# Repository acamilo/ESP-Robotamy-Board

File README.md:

## ESP8266 Robotics Board ##

The ESP-Robotics-Board is an arduino compatible board intended for building robots out of old toys as well as many other simple robotics projects.

- ESP8266-12 wifi module
- Dual L9110 (800ma) H-Bridge ICs
 - For small DC motors.
- ALC5628 DAC+AMP
 - Drive an 8 0hm speaker
- Screw Terminals to attatch motors, bettery, speakers
 - Strip wires in up-cycled toys and attatch directly to the board.
- Drive up to 8 servoes
 - 1 motor, 6 servoes
 - 2 motors, 4 servoes
 - 8 GPIO for sensors
  -i2c broken out
  -ADC broken out

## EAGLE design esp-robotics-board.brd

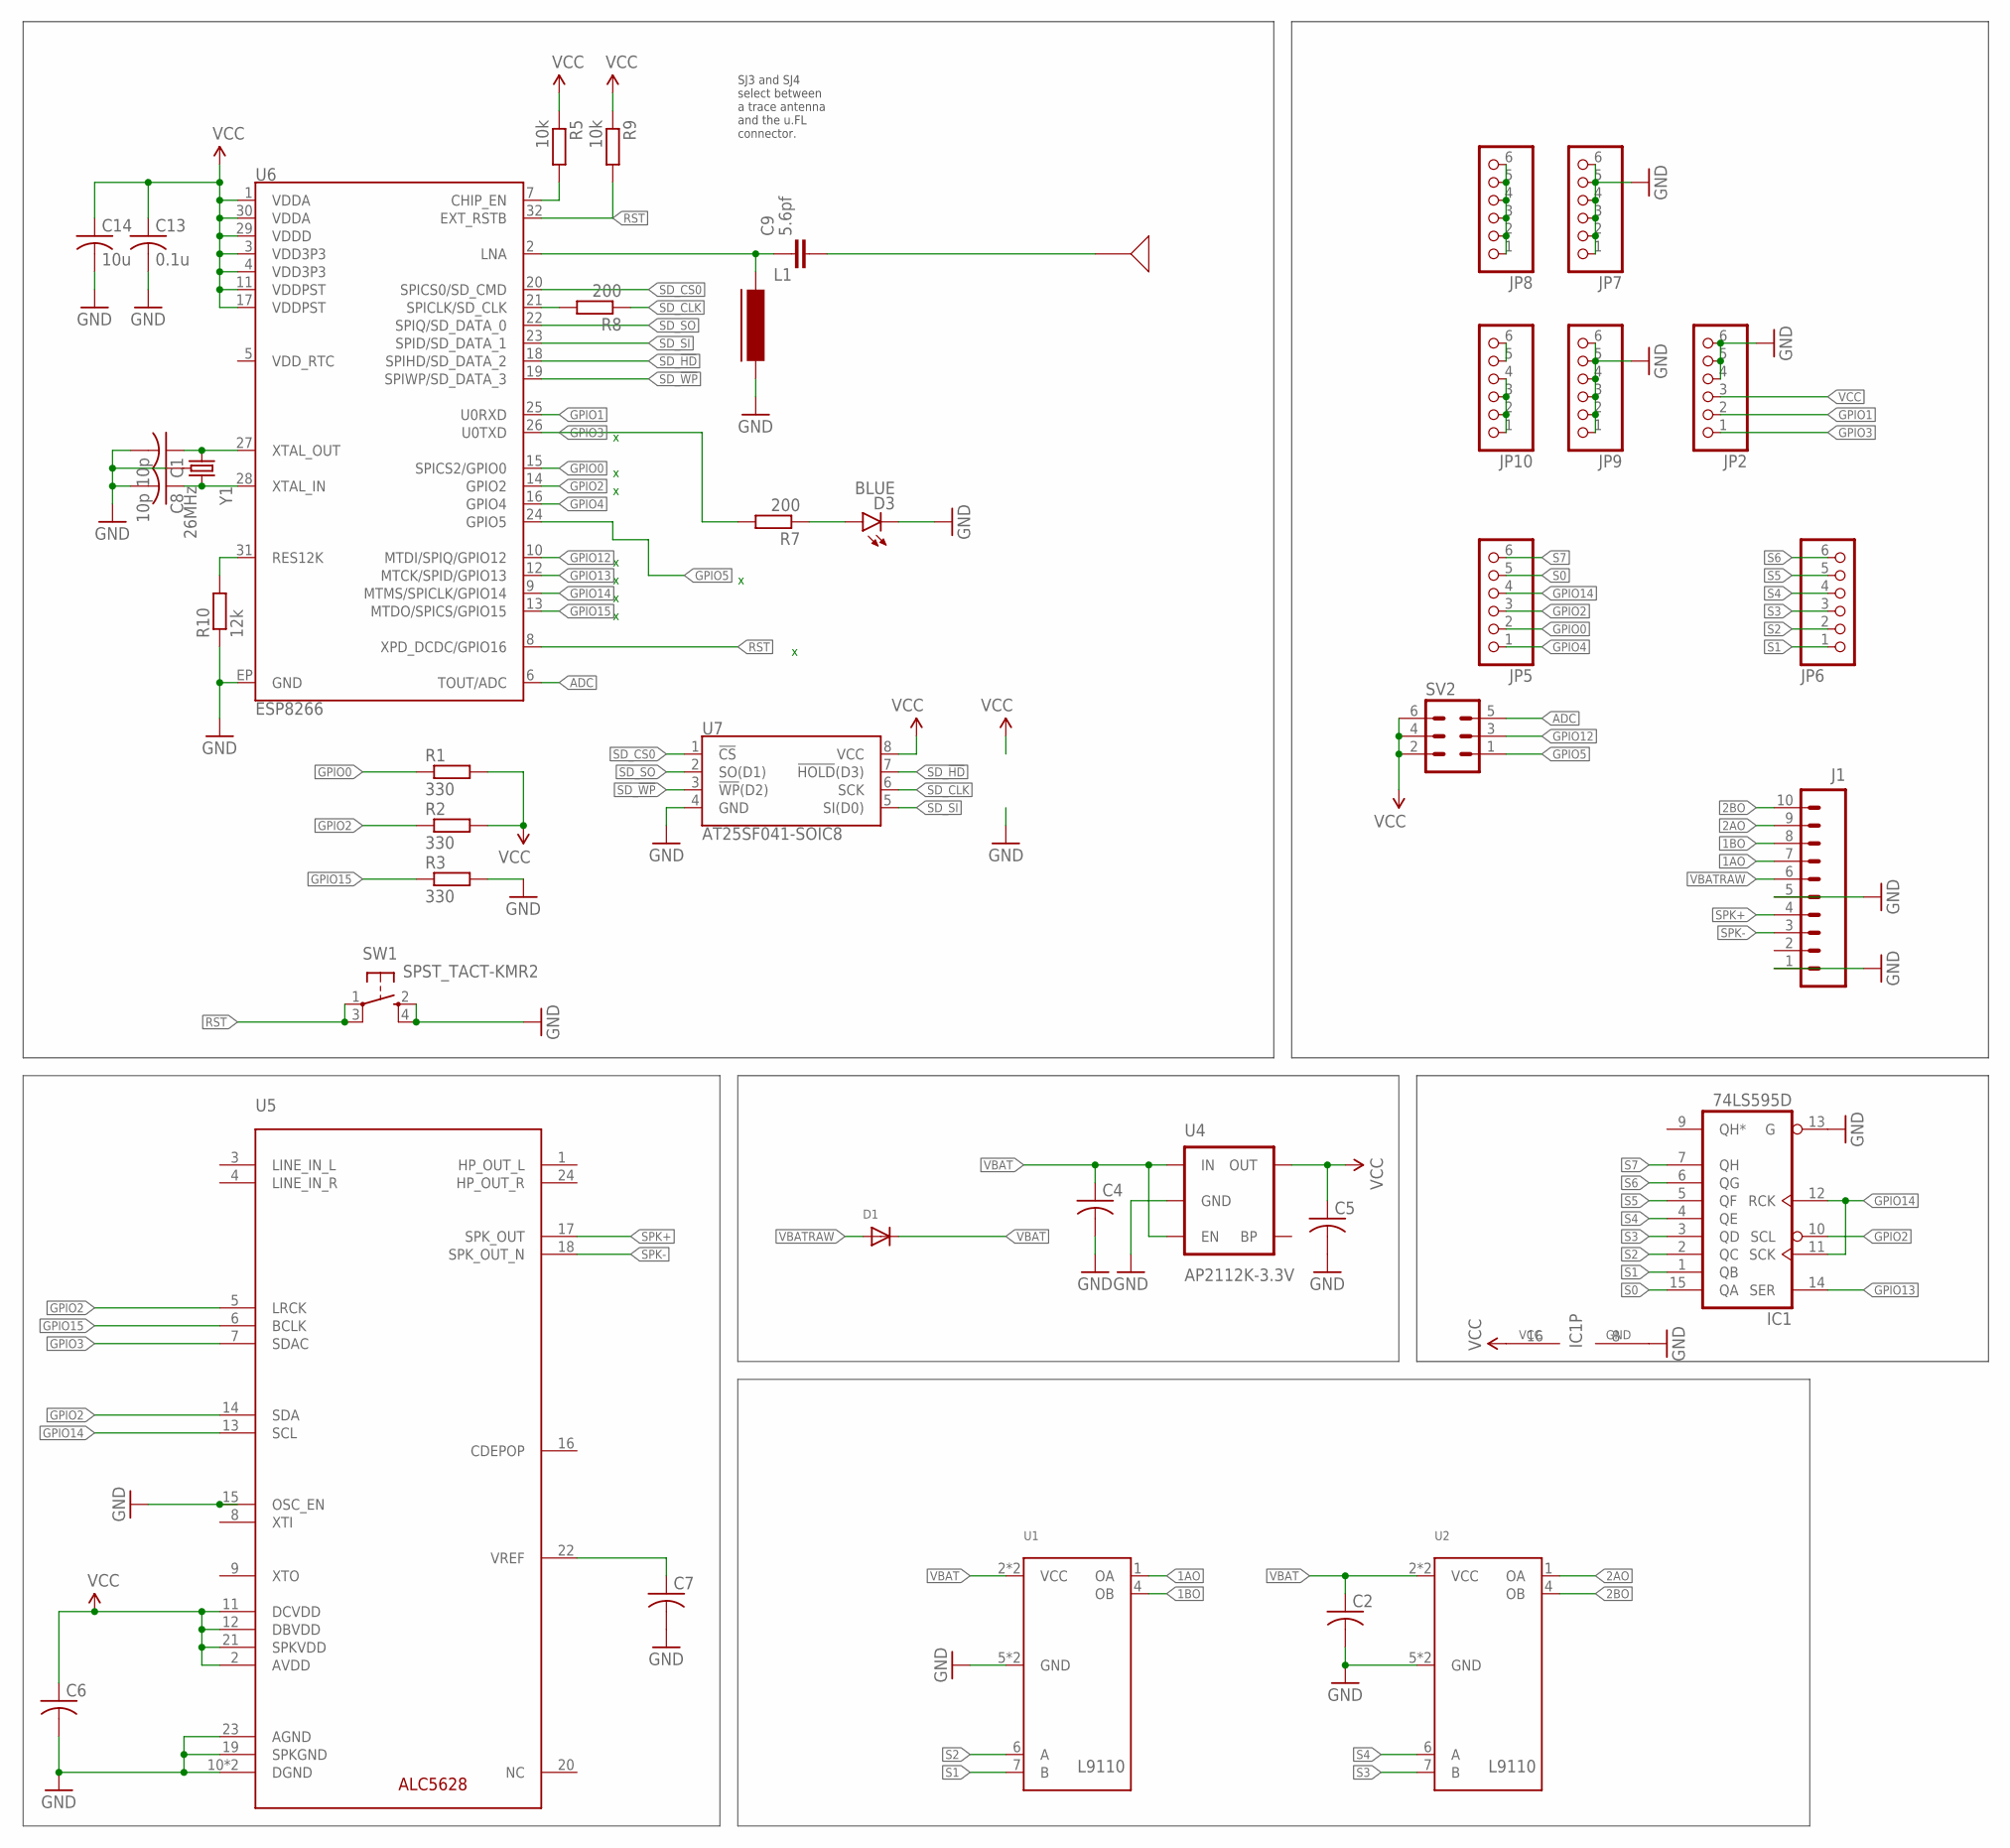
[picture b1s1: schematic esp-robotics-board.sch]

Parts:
C1, C8: 10p; C0402
C2, C4, C5: C-USC0805; C0805
C6, C7: C-USC0402; C0402
C9: 5.6pf; C402
C13: 0.1u; C0402
C14: 10u; C0402
D1: DIODESMA; SMADIODE
D3: BLUE; LED-0603
IC1: 74LS595D; SO16
J1: M10SILK_FEMALE_PTH; 1X10
JP2, JP5, JP6, JP7, JP8, JP9, JP10: PINHD-1X6; 1X06
L1: FERRITE-0402; FB402
R1, R2, R3: 330; R0402
R5, R9: 10k; R0402
R7, R8: 200; R0402
R10: 12k; R0402
SV2: MA03-2
SW1: SPST_TACT-KMR2; KMR2
U1, U2: L9110SMT; 8S1
U4: AP2112K-3.3V; SOT23-5
U5: ALC5628; QFN24
U6: ESP8266; QFN32
U7: AT25SF041-SOIC8; SO08
U$1: AN9520
Y1: 26MHz; CRYSTAL-SMD-3.2X2.5

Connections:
1AO: J1.7, U1.1 (OA)
1BO: J1.8, U1.4 (OB)
2AO: J1.9, U2.1 (OA)
2BO: J1.10, U2.4 (OB)
ADC: SV2.5, U6.6 (TOUT/ADC)
CHIP_EN: R5.2, U6.7 (CHIP_EN)
GND: C1.2, C2.2, C4.2, C5.2, C6.2, C7.2, C8.2, C13.2, C14.2, D3.C, IC1.8 (GND), IC1.13 (G), J1.1, J1.5, JP2.4, JP2.5, JP2.6, JP7.1, JP7.2, JP7.3, JP7.4, JP7.5, JP7.6, JP9.1, JP9.2, JP9.3, JP9.4, JP9.5, JP9.6, L1.2, R3.2, R10.1, SW1.2 (S), SW1.4 (S1), U1.5 (GND), U1.8 (GND), U2.5 (GND), U2.8 (GND), U4.2 (GND), U5.10 (DGND), U5.19 (SPKGND), U5.23 (AGND), U5.PAD (DGND), U6.EP (GND), U7.4 (GND), Y1.2 (GND), Y1.4 (GND)
GPIO0: JP5.2, R1.1, U6.15 (SPICS2/GPIO0)
GPIO1: JP2.2, U6.25 (U0RXD)
GPIO2: IC1.10 (SCL), JP5.3, R2.1, U5.5 (LRCK), U5.14 (SDA), U6.14 (GPIO2)
GPIO3: JP2.1, R7.2, U5.7 (SDAC), U6.26 (U0TXD)
GPIO4: JP5.1, U6.16 (GPIO4)
GPIO5: SV2.1, U6.24 (GPIO5)
GPIO12: SV2.3, U6.10 (MTDI/SPIQ/GPIO12)
GPIO13: IC1.14 (SER), U6.12 (MTCK/SPID/GPIO13)
GPIO14: IC1.11 (SCK), IC1.12 (RCK), JP5.4, U5.13 (SCL), U6.9 (MTMS/SPICLK/GPIO14)
GPIO15: R3.1, U5.6 (BCLK), U6.13 (MTDO/SPICS/GPIO15)
LNA: C9.1, L1.1, U6.2 (LNA)
LNA2: C9.2, U$1.FEED
unnamed: D3.A, R7.1
unnamed: C7.1, U5.22 (VREF)
unnamed: R10.2, U6.31 (RES12K)
unnamed: C8.1, U6.28 (XTAL_IN), Y1.3 (2)
unnamed: C1.1, U6.27 (XTAL_OUT), Y1.1
RST: R9.2, SW1.1, SW1.3 (P1), U6.8 (XPD_DCDC/GPIO16), U6.32 (EXT_RSTB)
S0: IC1.15 (QA), JP5.5
S1: IC1.1 (QB), JP6.1, U1.7 (B)
S2: IC1.2 (QC), JP6.2, U1.6 (A)
S3: IC1.3 (QD), JP6.3, U2.7 (B)
S4: IC1.4 (QE), JP6.4, U2.6 (A)
S5: IC1.5 (QF), JP6.5
S6: IC1.6 (QG), JP6.6
S7: IC1.7 (QH), JP5.6
SD_!HD!: U6.18 (SPIHD/SD_DATA_2), U7.7 (!HOLD!(D3))
SD_!WP!: U6.19 (SPIWP/SD_DATA_3), U7.3 (!WP!(D2))
SD_CLK: R8.1, U7.6 (SCK)
SD_CLK0: R8.2, U6.21 (SPICLK/SD_CLK)
SD_CS0: U6.20 (SPICS0/SD_CMD), U7.1 (!CS!)
SD_SI: U6.23 (SPID/SD_DATA_1), U7.5 (SI(D0))
SD_SO: U6.22 (SPIQ/SD_DATA_0), U7.2 (SO(D1))
SPK+: J1.4, U5.17 (SPK_OUT)
SPK-: J1.3, U5.18 (SPK_OUT_N)
VBAT: C2.1, C4.1, D1.C, JP8.1, JP8.2, JP8.3, JP8.4, JP8.5, JP8.6, JP10.5, JP10.6, U1.2 (VCC), U1.3 (VCC), U2.2 (VCC), U2.3 (VCC), U4.1 (IN), U4.3 (EN)
VBATRAW: D1.A, J1.6
VCC: C5.1, C6.1, C13.1, C14.1, IC1.16 (VCC), JP2.3, JP10.1, JP10.2, JP10.3, JP10.4, R1.2, R2.2, R5.1, R9.1, SV2.2, SV2.4, SV2.6, U4.5 (OUT), U5.2 (AVDD), U5.11 (DCVDD), U5.12 (DBVDD), U5.21 (SPKVDD), U6.1 (VDDA), U6.3 (VDD3P3), U6.4 (VDD3P3), U6.11 (VDDPST), U6.17 (VDDPST), U6.29 (VDDD), U6.30 (VDDA), U7.8 (VCC)

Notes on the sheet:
SJ3 and SJ4 select between a trace antenna and the u.FL connector.

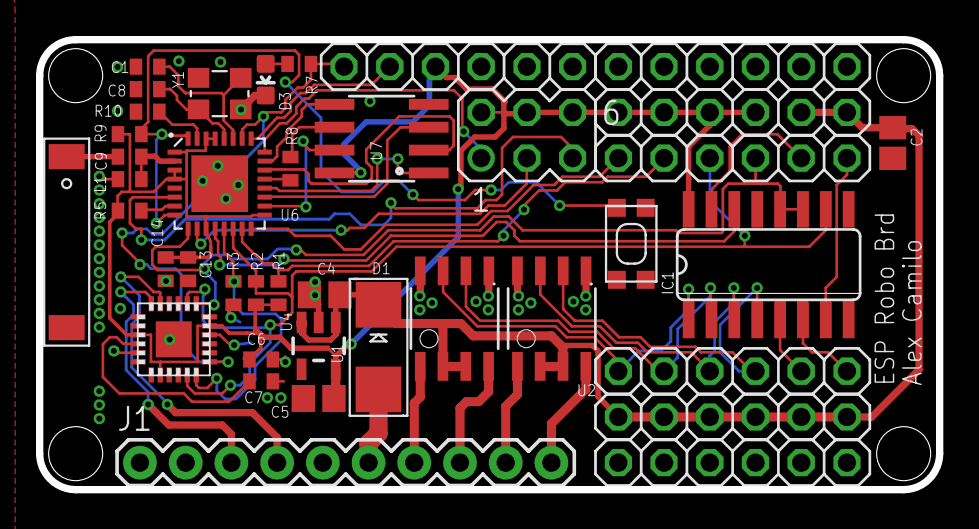
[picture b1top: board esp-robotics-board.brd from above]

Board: 2 copper layers, 50.0 x 25.0 mm, 40 parts (0 on the bottom side), 45 nets.

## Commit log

2016-03-28 Created repo, added files

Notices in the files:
parts and their libraries:
SparkFun-Connectors: Licensing: Creative Commons ShareAlike 4.0 International - https://creativecommons.org/licenses/by-sa/4.0
